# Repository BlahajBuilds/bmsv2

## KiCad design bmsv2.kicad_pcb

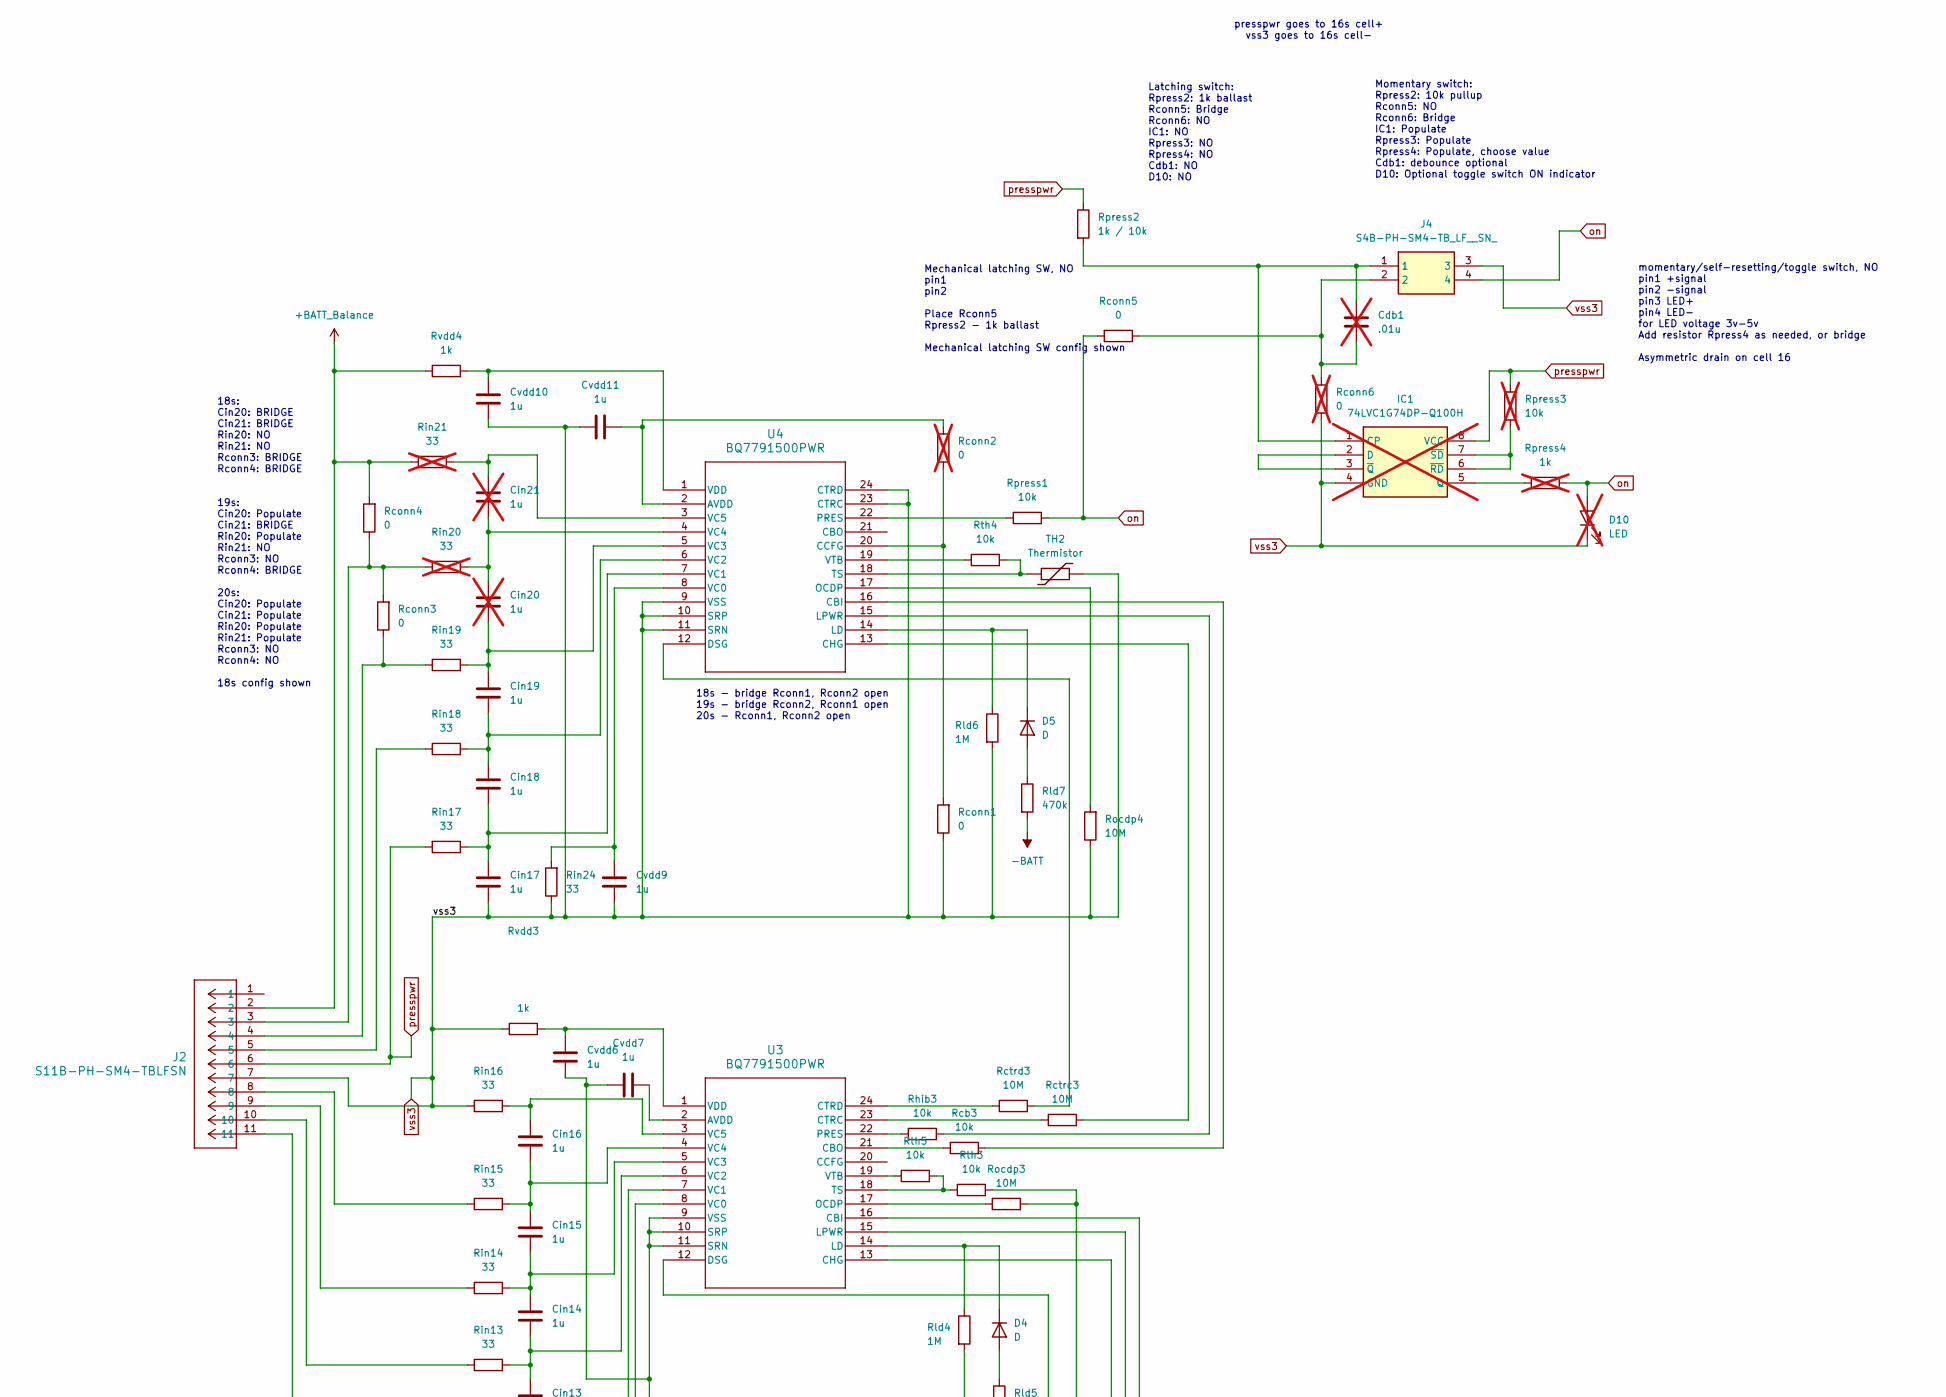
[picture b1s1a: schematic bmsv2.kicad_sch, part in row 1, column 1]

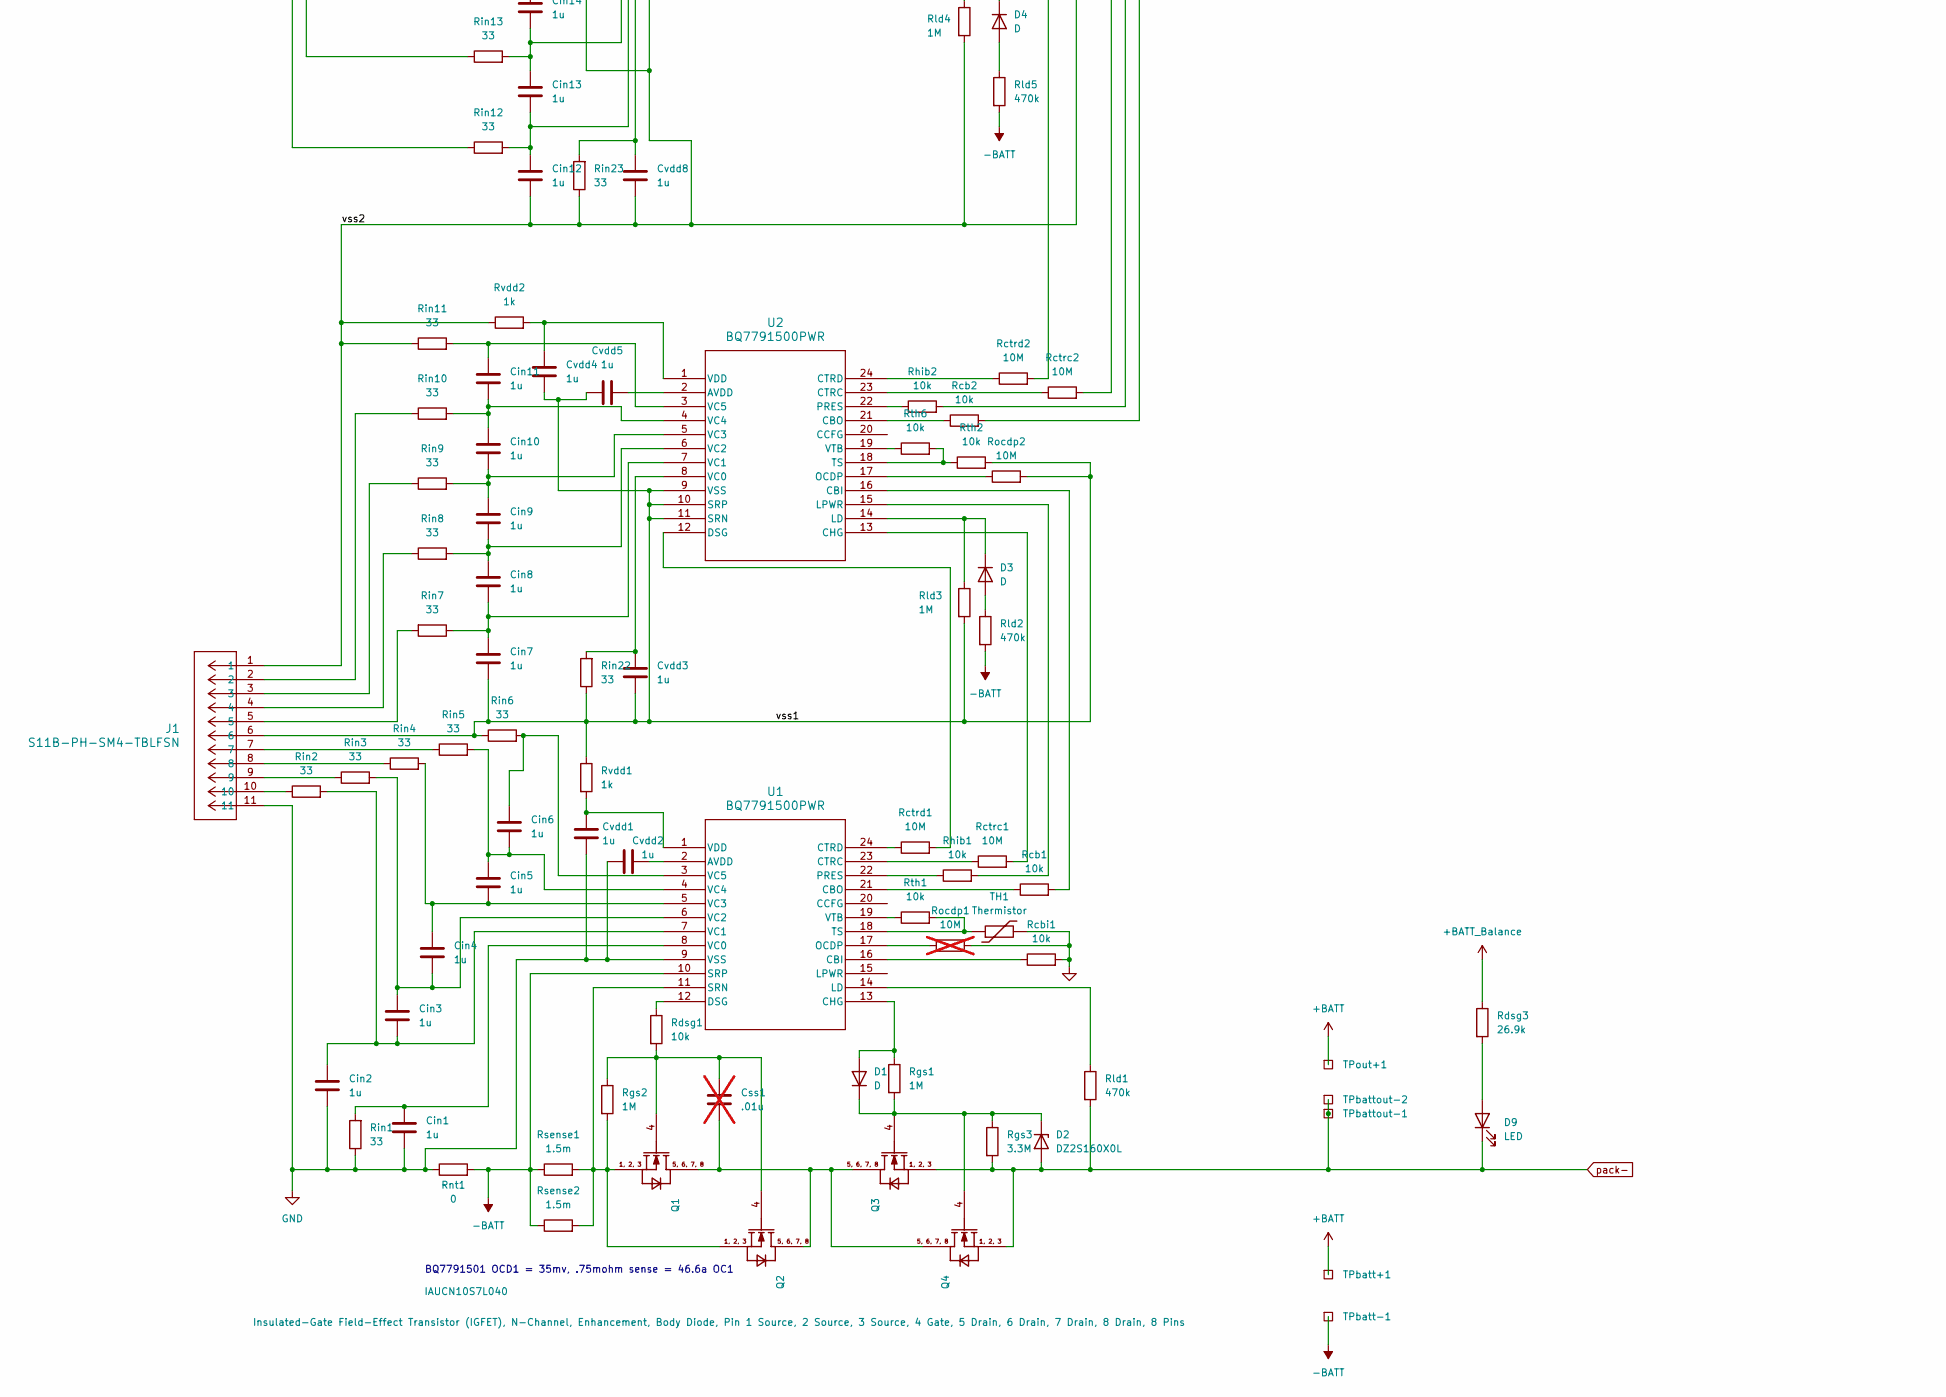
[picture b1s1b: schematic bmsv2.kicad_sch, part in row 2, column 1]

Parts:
Cdb1: .01u; C_0603_1608Metric; not fitted
Cin1, Cin2, Cin3, Cin4, Cin5, Cin6, Cin7, Cin8, Cin9, Cin10, Cin11, Cin12, Cin13, Cin14, Cin15, Cin16, Cin17, Cin18, Cin19: 1u; C_0603_1608Metric
Cin20, Cin21: 1u; C_0603_1608Metric; not fitted
Css1: .01u; C_0603_1608Metric; not fitted
Cvdd1, Cvdd2, Cvdd3, Cvdd4, Cvdd5, Cvdd6, Cvdd7, Cvdd8, Cvdd9, Cvdd10, Cvdd11: 1u; C_0603_1608Metric
D1, D3, D4, D5: D; D_SOD-323
D2: DZ2S160X0L; D_SOD-323
D9: LED; LED_0603_1608Metric
D10: LED; LED_0603_1608Metric; not fitted
IC1: 74LVC1G74DP-Q100H; SOP65P400X110-8N; Mouser Part Number 771-74LVC1G74DPQ100H; not fitted
J1, J2: S11B-PH-SM4-TBLFSN; CONN_S11B-PH-SM4-TB_JST
J4: S4B-PH-SM4-TB_LF__SN_; S4B-PH-SM4-TB; Mouser Part Number N/A
Q1, Q2, Q3, Q4: IAUCN10S7L040; IPC100N04S51R2ATMA1
Rcb1, Rcb2, Rcb3: 10k; R_0603_1608Metric
Rcbi1: 10k; R_0603_1608Metric
Rconn1, Rconn3, Rconn4, Rconn5: 0; R_0603_1608Metric
Rconn2, Rconn6: 0; R_0603_1608Metric; not fitted
Rctrc1, Rctrc2, Rctrc3: 10M; R_0603_1608Metric
Rctrd1, Rctrd2, Rctrd3: 10M; R_0603_1608Metric
Rdsg1: 10k; R_0603_1608Metric
Rdsg3: 26.9k; R_0805_2012Metric
Rgs1, Rgs2: 1M; R_0603_1608Metric
Rgs3: 3.3M; R_0603_1608Metric
Rhib1, Rhib2, Rhib3: 10k; R_0603_1608Metric
Rin1, Rin2, Rin3, Rin4, Rin5, Rin6, Rin7, Rin8, Rin9, Rin10, Rin11, Rin12, Rin13, Rin14, Rin15, Rin16, Rin17, Rin18, Rin19, Rin22, Rin23, Rin24: 33; R_0603_1608Metric
Rin20, Rin21: 33; R_0603_1608Metric; not fitted
Rld1, Rld2, Rld5, Rld7: 470k; R_0603_1608Metric
Rld3, Rld4, Rld6: 1M; R_0603_1608Metric
Rnt1: 0; R_0805_2012Metric
Rocdp1: 10M; R_0603_1608Metric; not fitted
Rocdp2, Rocdp3, Rocdp4: 10M; R_0603_1608Metric
Rpress1: 10k; R_0603_1608Metric
Rpress2: 1k / 10k; R_0603_1608Metric
Rpress3: 10k; R_0603_1608Metric; not fitted
Rpress4: 1k; R_0603_1608Metric; not fitted
Rsense1, Rsense2: 1.5m; R_2512_6332Metric
Rth1, Rth2, Rth3, Rth4, Rth5, Rth6: 10k; R_0603_1608Metric
Rvdd1, Rvdd2, Rvdd3, Rvdd4: 1k; R_0603_1608Metric
TH1, TH2: Thermistor; R_0603_1608Metric
TPbatt+1: TestPoint_Square; TestPoint_Pad_4.0x4.0mm
TPbatt-1: TestPoint_Square; TestPoint_Pad_4.0x4.0mm
TPbattout-1, TPbattout-2: TestPoint_Square; TestPoint_Pad_4.0x4.0mm
TPout+1: TestPoint_Square; TestPoint_Pad_4.0x4.0mm
U1, U2, U3, U4: BQ7791500PWR; PW24_TEX-L

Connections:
+BATT: TPbatt+1.1 (1_1), TPout+1.1 (1_1)
+BATT_Balance: J2.2, Rconn4.2, Rdsg3.1, Rin21.1, Rvdd4.1
-BATT: Rld2.2, Rld5.2, Rld7.2, Rnt1.2, Rsense1.1, Rsense2.1, TPbatt-1.1 (1_1), U1.10 (SRP)
/vss1: Cin7.2, Cvdd3.1, Cvdd4.2, Cvdd5.1, J1.6, Rin6.1, Rin22.1, Rld3.2, Rocdp2.2, Rth2.2, Rvdd1.1, U2.9 (VSS), U2.10 (SRP), U2.11 (SRN)
/vss2: Cin12.2, Cvdd6.2, Cvdd7.1, Cvdd8.1, J1.1, Rin11.1, Rin23.1, Rld4.2, Rocdp3.2, Rth3.2, Rvdd2.1, U3.9 (VSS), U3.10 (SRP), U3.11 (SRN)
GND: Cin1.2, Cin2.2, Cvdd1.1, Cvdd2.2, J1.11, Rcbi1.2, Rin1.1, Rnt1.1, Rocdp1.2, TH1.2, U1.9 (VSS)
unnamed: Cdb1.2, J4.2, Rconn5.1, Rconn6.1
unnamed: Css1.2, Q1.5 (DRAIN), Q1.6 (DRAIN), Q1.7 (DRAIN), Q1.8 (DRAIN), Q2.5 (DRAIN), Q2.6 (DRAIN), Q2.7 (DRAIN), Q2.8 (DRAIN), Q3.5 (DRAIN), Q3.6 (DRAIN), Q3.7 (DRAIN), Q3.8 (DRAIN), Q4.5 (DRAIN), Q4.6 (DRAIN), Q4.7 (DRAIN), Q4.8 (DRAIN)
unnamed: D1.2 (A), Rgs1.1, U1.13 (CHG)
unnamed: D1.1 (K), D2.1 (K), Q3.4 (GATE), Q4.4 (GATE), Rgs1.2, Rgs3.1
unnamed: D3.2 (A), Rld2.1
unnamed: D3.1 (K), Rld3.1, U2.14 (LD)
unnamed: D4.2 (A), Rld5.1
unnamed: D4.1 (K), Rld4.1, U3.14 (LD)
unnamed: D5.2 (A), Rld7.1
unnamed: D5.1 (K), Rld6.1, U4.14 (LD)
unnamed: D9.2 (A), Rdsg3.2
unnamed: Cdb1.1, IC1.1 (CP), J4.1, Rpress2.2
unnamed: IC1.2 (D), IC1.3 (~Q)
unnamed: IC1.5 (Q), Rpress4.1
unnamed: IC1.6 (~RD), IC1.7 (~SD), Rpress3.1
unnamed: J1.2, Rin10.1
unnamed: J1.3, Rin9.1
unnamed: J1.4, Rin8.1
unnamed: J1.5, Rin7.2
unnamed: J1.7, Rin5.1
unnamed: J1.8, Rin4.1
unnamed: J1.9, Rin3.1
unnamed: J1.10, Rin2.1
unnamed: J2.3, Rconn3.2, Rconn4.1, Rin20.1
unnamed: J2.4, Rconn3.1, Rin19.1
unnamed: J2.5, Rin18.1
unnamed: J2.8, Rin15.1
unnamed: J2.9, Rin14.1
unnamed: J2.10, Rin13.1
unnamed: J2.11, Rin12.1
unnamed: Css1.1, Q1.4 (GATE), Q2.4 (GATE), Rdsg1.2, Rgs2.1
unnamed: Cvdd2.1, U1.2 (AVDD)
unnamed: Rcbi1.1, U1.16 (CBI)
unnamed: Rcb1.1, U1.21 (CBO)
unnamed: Rctrc1.1, U1.23 (CTRC)
unnamed: Rctrd1.1, U1.24 (CTRD)
unnamed: Rdsg1.1, U1.12 (DSG)
unnamed: Rld1.1, U1.14 (LD)
unnamed: Rocdp1.1, U1.17 (OCDP)
unnamed: Rhib1.1, U1.22 (PRES)
unnamed: Q1.1 (SOURCE), Q1.2 (SOURCE), Q1.3 (SOURCE), Q2.1 (SOURCE), Q2.2 (SOURCE), Q2.3 (SOURCE), Rgs2.2, Rsense1.2, Rsense2.2, U1.11 (SRN)
unnamed: Rth1.2, TH1.1, U1.18 (TS)
unnamed: Cin1.1, Rin1.2, U1.8 (VC0)
unnamed: Cin2.1, Cin3.2, Rin2.2, U1.7 (VC1)
unnamed: Cin3.1, Cin4.2, Rin3.2, U1.6 (VC2)
unnamed: Cin4.1, Cin5.2, Rin4.2, U1.5 (VC3)
unnamed: Cin5.1, Cin6.2, Rin5.2, U1.4 (VC4)
unnamed: Cin6.1, Rin6.2, U1.3 (VC5)
unnamed: Cvdd1.2, Rvdd1.2, U1.1 (VDD)
unnamed: Rth1.1, U1.19 (VTB)
unnamed: Cvdd5.2, U2.2 (AVDD)
unnamed: Rcb1.2, U2.16 (CBI)
unnamed: Rcb2.1, U2.21 (CBO)
unnamed: Rctrc1.2, U2.13 (CHG)
unnamed: Rctrc2.1, U2.23 (CTRC)
unnamed: Rctrd2.1, U2.24 (CTRD)
unnamed: Rctrd1.2, U2.12 (DSG)
unnamed: Rhib1.2, U2.15 (LPWR)
unnamed: Rocdp2.1, U2.17 (OCDP)
unnamed: Rhib2.1, U2.22 (PRES)
unnamed: Rth2.1, Rth6.2, U2.18 (TS)
unnamed: Cvdd3.2, Rin22.2, U2.8 (VC0)
unnamed: Cin7.1, Cin8.2, Rin7.1, U2.7 (VC1)
unnamed: Cin8.1, Cin9.2, Rin8.2, U2.6 (VC2)
unnamed: Cin9.1, Cin10.2, Rin9.2, U2.5 (VC3)
unnamed: Cin10.1, Cin11.2, Rin10.2, U2.4 (VC4)
unnamed: Cin11.1, Rin11.2, U2.3 (VC5)
unnamed: Cvdd4.1, Rvdd2.2, U2.1 (VDD)
unnamed: Rth6.1, U2.19 (VTB)
unnamed: Cvdd7.2, U3.2 (AVDD)
unnamed: Rcb2.2, U3.16 (CBI)
unnamed: Rcb3.1, U3.21 (CBO)
unnamed: Rctrc2.2, U3.13 (CHG)
unnamed: Rctrc3.1, U3.23 (CTRC)
unnamed: Rctrd3.1, U3.24 (CTRD)
unnamed: Rctrd2.2, U3.12 (DSG)
unnamed: Rhib2.2, U3.15 (LPWR)
unnamed: Rocdp3.1, U3.17 (OCDP)
unnamed: Rhib3.1, U3.22 (PRES)
unnamed: Rth3.1, Rth5.2, U3.18 (TS)
unnamed: Cvdd8.2, Rin23.2, U3.8 (VC0)
unnamed: Cin12.1, Cin13.2, Rin12.2, U3.7 (VC1)
unnamed: Cin13.1, Cin14.2, Rin13.2, U3.6 (VC2)
unnamed: Cin14.1, Cin15.2, Rin14.2, U3.5 (VC3)
unnamed: Cin15.1, Cin16.2, Rin15.2, U3.4 (VC4)
unnamed: Cin16.1, Rin16.2, U3.3 (VC5)
unnamed: Cvdd6.1, Rvdd3.2, U3.1 (VDD)
unnamed: Rth5.1, U3.19 (VTB)
unnamed: Cvdd11.2, Rconn2.2, U4.2 (AVDD)
unnamed: Rcb3.2, U4.16 (CBI)
unnamed: Rconn1.2, Rconn2.1, U4.20 (CCFG)
unnamed: Rctrc3.2, U4.13 (CHG)
unnamed: Rctrd3.2, U4.12 (DSG)
unnamed: Rhib3.2, U4.15 (LPWR)
unnamed: Rocdp4.2, U4.17 (OCDP)
unnamed: Rpress1.1, U4.22 (PRES)
unnamed: Rth4.2, TH2.1, U4.18 (TS)
unnamed: Cvdd9.2, Rin24.2, U4.8 (VC0)
unnamed: Cin17.1, Cin18.2, Rin17.1, U4.7 (VC1)
unnamed: Cin18.1, Cin19.2, Rin18.2, U4.6 (VC2)
unnamed: Cin19.1, Cin20.2, Rin19.2, U4.5 (VC3)
unnamed: Cin20.1, Cin21.2, Rin20.2, U4.4 (VC4)
unnamed: Cin21.1, Rin21.2, U4.3 (VC5)
unnamed: Cvdd10.1, Rvdd4.2, U4.1 (VDD)
unnamed: Rth4.1, U4.19 (VTB)
on: D10.2 (A), J4.4, Rconn5.2, Rpress1.2, Rpress4.2
pack-: D2.2 (A), D9.1 (K), Q3.1 (SOURCE), Q3.2 (SOURCE), Q3.3 (SOURCE), Q4.1 (SOURCE), Q4.2 (SOURCE), Q4.3 (SOURCE), Rgs3.2, Rld1.2, TPbattout-1.1 (1_1), TPbattout-2.1 (1_1)
presspwr: IC1.8 (VCC), J2.6, Rin17.2, Rpress2.1, Rpress3.2
vss3: Cin17.2, Cvdd9.1, Cvdd10.2, Cvdd11.1, D10.1 (K), IC1.4 (GND), J2.7, J4.3, Rconn1.1, Rconn6.2, Rin16.1, Rin24.1, Rld6.2, Rocdp4.1, Rvdd3.1, TH2.2, U4.9 (VSS), U4.10 (SRP), U4.11 (SRN), U4.23 (CTRC), U4.24 (CTRD)

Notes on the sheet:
presspwr goes to 16s cell+ vss3 goes to 16s cell-
momentary/self-resetting/toggle switch, NO pin1 +signal pin2 -signal pin3 LED+ pin4 LED- for LED voltage 3v-5v Add resistor Rpress4 as needed, or bridge Asymmetric drain on cell 16
BQ7791501 OCD1 = 35mv, .75mohm sense = 46.6a OC1
18s - bridge Rconn1, Rconn2 open 19s - bridge Rconn2, Rconn1 open 20s - Rconn1, Rconn2 open
Momentary switch: Rpress2: 10k pullup Rconn5: NO Rconn6: Bridge IC1: Populate Rpress3: Populate Rpress4: Populate, choose value Cdb1: debounce optional D10: Optional toggle switch ON indicator
Latching switch: Rpress2: 1k ballast Rconn5: Bridge Rconn6: NO IC1: NO Rpress3: NO Rpress4: NO Cdb1: NO D10: NO
Mechanical latching SW, NO pin1 pin2 Place Rconn5 Rpress2 - 1k ballast Mechanical latching SW config shown
18s: Cin20: BRIDGE Cin21: BRIDGE Rin20: NO Rin21: NO Rconn3: BRIDGE Rconn4: BRIDGE 19s: Cin20: Populate Cin21: BRIDGE Rin20: Populate Rin21: NO Rconn3: NO Rconn4: BRIDGE 20s: Cin20: Populate Cin21: Populate Rin20: Populate Rin21: Populate Rconn3: NO Rconn4: NO 18s config shown

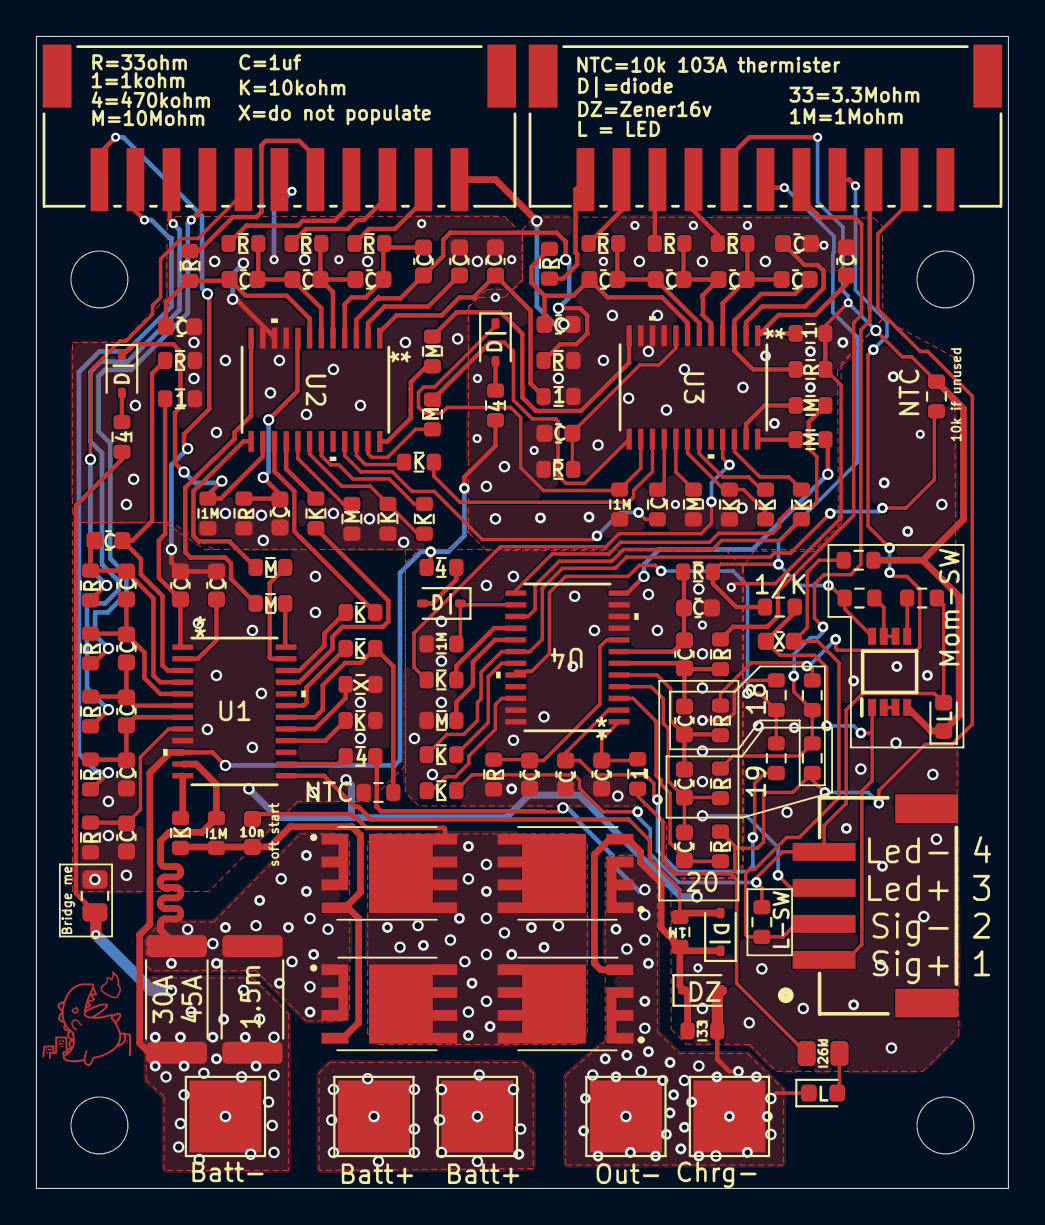
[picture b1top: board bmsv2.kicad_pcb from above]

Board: 2 copper layers, 54.0 x 64.0 mm, 136 parts (0 on the bottom side), 115 nets.
